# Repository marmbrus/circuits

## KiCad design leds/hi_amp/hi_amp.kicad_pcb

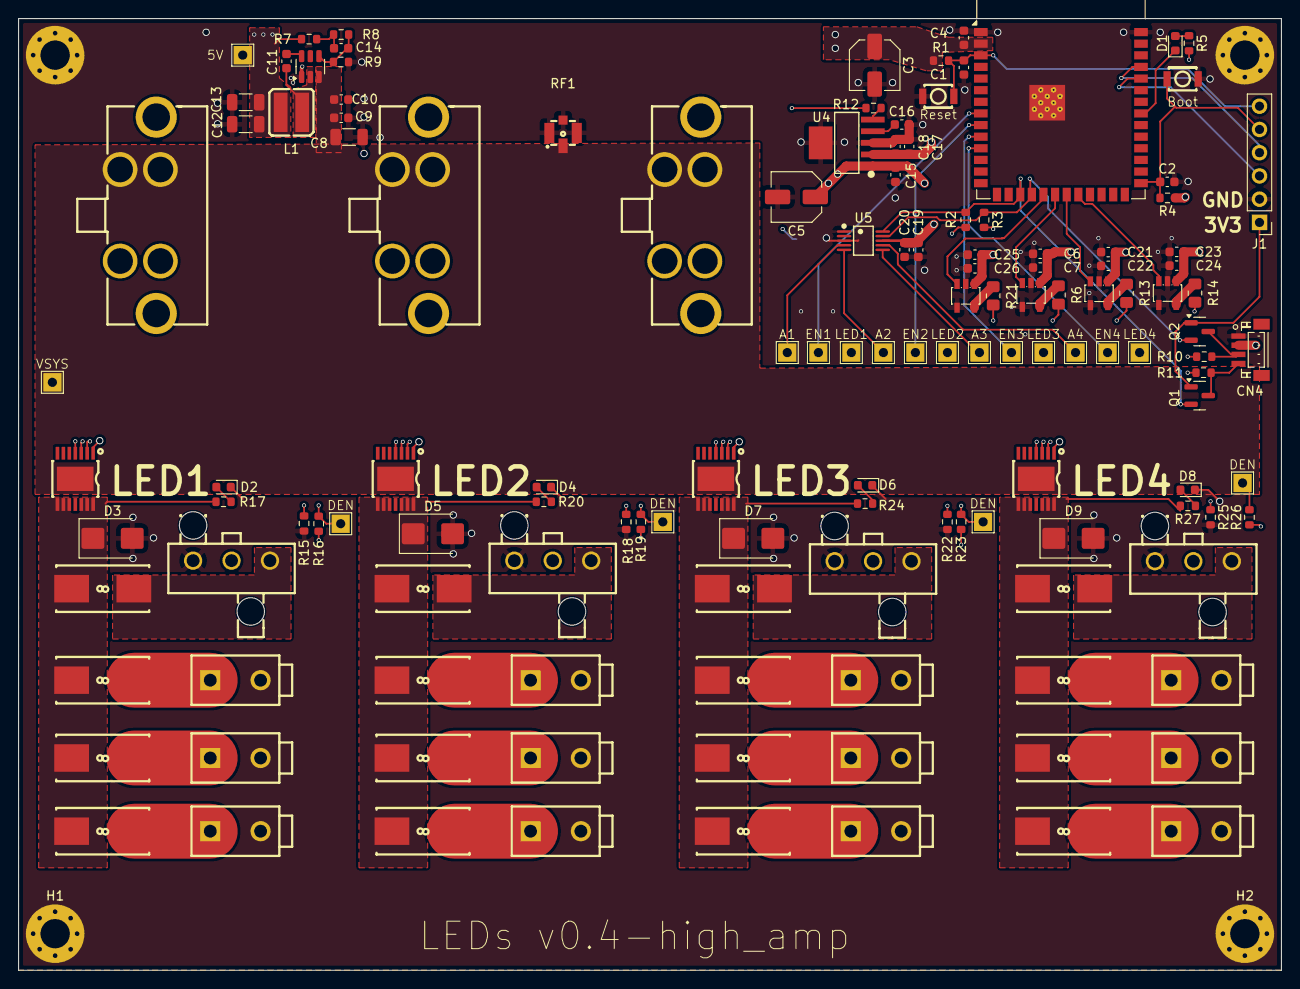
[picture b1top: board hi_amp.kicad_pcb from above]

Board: 4 copper layers, 138.0 x 104.0 mm, 140 parts (1 on the bottom side), 68 nets.

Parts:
C1: 10uf; C_0603_1608Metric
C2: 1uf; C_0603_1608Metric
C3, C5: 22uF; C_Elec_5x5.8
C4, C7, C10, C20, C22, C24, C26: 100nF; C_0603_1608Metric
C6, C9, C21, C23, C25: 10uF; C_0603_1608Metric
C8, C12, C13: 22uF; C_1206_3216Metric
C11: 100nf; C_0603_1608Metric
C14: 75pF; C_0603_1608Metric
C15, C17, C18, C19: 1uF; C_0603_1608Metric
C16: 10nF; C_0603_1608Metric
CN1, CN2, CN3: 428192213; CONN-TH_0428192214
CN4: BM04B-SRSS-TB(LF)(SN); CONN-SMD_BM04B-SRSS-TB
CN5, CN9, CN13, CN17: 39302030; CONN-TH_3P-P4.20_39302030
CN6, CN7, CN8, CN10, CN11, CN12, CN14, CN15, CN16, CN18, CN19, CN20: 39288020; CONN-TH_39288020
D1, D2, D4, D6, D8: LED; LED_0603_1608Metric
D3, D5, D7, D9: D_TVS; D_SMB
FH1, FH2, FH3, FH4, FH5, FH6, FH7, FH8, FH9, FH10, FH11, FH12, FH13, FH14, FH15, FH16: 01550900M; FUSE-SMD_L9.8-W5.0_01550900M
H1, H2, H3, H4: MountingHole_Pad; MountingHole_3.2mm_M3_Pad_Via
J1: Conn_01x06; PinHeader_1x06_P2.54mm_Vertical
L1: XGL4040-153MEC; IND-SMD_L4.0-W4.0_XAL4040-103
Q1, Q2: BSS138; SOT-23
R1, R2, R3, R4, R10, R11, R12: 10k; R_0603_1608Metric
R5: 330; R_0603_1608Metric
R6, R13, R14, R21: 120; R_0805_2012Metric_Pad1.20x1.40mm_HandSolder
R7: 49.9; R_0603_1608Metric
R8: 100k; R_0603_1608Metric
R9: 13.3k; R_0603_1608Metric
R15, R18, R22, R25: 1.5k; R_0603_1608Metric
R16, R19, R23, R26: 4.7k; R_0603_1608Metric
R17, R20, R24, R27: 3.3k; R_0603_1608Metric
RF1, RF2: 73412-0110; ANT-SMD_73412-0110
SW1, SW2: KEY-SMD_B3U-1000PM
TP1, TP2, TP3, TP4, TP5, TP6, TP7, TP8, TP9, TP10, TP11, TP12, TP13, TP14, TP15, TP16, TP17, TP18: LabeledTestPoint
U1: ESP32-S3-WROOM-1
U2, U6, U7, U10: UCC27517DBVR; SOT-23-5_L3.0-W1.7-P0.95-LS2.8-BR
U3: TPS54202DDC; SOT-23-6
U4: TPS73733DCQ_C5220270; SOT-223-6_L6.5-W3.5-P1.27-LS7.0-BR
U5: ADS1115IDGSR; MSOP-10_L3.0-W3.0-P0.50-LS5.0-BL
U8, U9, U11, U12: BTS70021EPPXUMA1; PG-TSDSO-14_L4.9-W3.9-P0.65-LS6.0-BL-EP

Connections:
/3v3/3v3: C3.1, C4.1, C17.1, C18.1, J1.1, Q1.1 (G), Q2.1 (G), R1.1, R2.1, R3.1, R4.1, R5.2, U1.2 (3V3), U4.2 (OUT)
/5V: C5.1, C6.1, C7.1, C12.1, C13.1, C15.1, C19.1, C20.1, C21.1, C22.1, C23.1, C24.1, C25.1, C26.1, CN4.2, L1.2, R7.1, R10.1, R11.1, R12.1, R16.1, R19.1, R23.1, R26.1, RF2.2 (SIG), TP14.1, U2.1 (VDD), U4.1 (IN), U5.8 (VDD), U6.1 (VDD), U7.1 (VDD), U10.1 (VDD)
/VSYS: C8.1, C9.1, C10.1, CN1.2, CN1.4, CN2.2, CN2.4, CN3.2, CN3.4, RF1.2 (SIG), TP1.1, U3.3 (VIN), U8.15 (VS), U9.15 (VS), U11.15 (VS), U12.15 (VS)
/a2d/AIN1: R15.1, TP6.1, U5.4 (AIN0), U8.4 (IS)
/a2d/AIN2: R18.1, TP8.1, U5.5 (AIN1), U9.4 (IS)
/a2d/AIN3: R22.1, TP10.1, U5.6 (AIN2), U11.4 (IS)
/a2d/AIN4: R25.1, TP12.1, U5.7 (AIN3), U12.4 (IS)
/a2d/I2C.SCL: Q1.2 (S), R2.2, U1.17 (IO9), U5.10 (SCL)
/a2d/I2C.SDA: Q2.2 (S), R3.2, U1.18 (IO10), U5.9 (SDA)
/buckconverter/FB: C14.1, R8.2, R9.1, U3.4 (FB)
/buckconverter/SW: C11.2, L1.1, U3.2 (SW)
/esp32/EN1: TP7.1, U1.8 (IO15), U8.2 (IN)
/esp32/EN2: TP9.1, U1.9 (IO16), U9.2 (IN)
/esp32/EN3: TP11.1, U1.10 (IO17), U11.2 (IN)
/esp32/EN4: TP13.1, U1.11 (IO18), U12.2 (IN)
/esp32/LED1: CN5.2, R21.1, TP2.1
/esp32/LED2: CN9.2, R6.1, TP3.1
/esp32/LED3: CN13.2, R13.1, TP4.1
/esp32/LED4: CN17.2, R14.1, TP5.1
/esp32/driver1/IN: U1.20 (IO12), U2.3 (IN+)
/esp32/driver2/IN: U1.21 (IO13), U6.3 (IN+)
/esp32/driver3/IN: U1.22 (IO14), U7.3 (IN+)
/esp32/driver/IN: U1.19 (IO11), U10.3 (IN+)
/led_channel1/Fused1: CN9.1, FH5.2
/led_channel1/Switched12V: D5.1 (K), FH5.1, FH6.1, FH7.1, FH8.1, R20.1, U9.8 (OUT), U9.9 (OUT), U9.10 (OUT), U9.12 (OUT), U9.13 (OUT), U9.14 (OUT)
/led_channel2/Fused1: CN13.1, FH9.2
/led_channel2/Switched12V: D7.1 (K), FH9.1, FH10.1, FH11.1, FH12.1, R24.1, U11.8 (OUT), U11.9 (OUT), U11.10 (OUT), U11.12 (OUT), U11.13 (OUT), U11.14 (OUT)
/led_channel3/Fused1: CN17.1, FH13.2
/led_channel3/Switched12V: D9.1 (K), FH13.1, FH14.1, FH15.1, FH16.1, R27.1, U12.8 (OUT), U12.9 (OUT), U12.10 (OUT), U12.12 (OUT), U12.13 (OUT), U12.14 (OUT)
/led_channel/Fused1: CN5.1, FH1.2
/led_channel/Switched12V: D3.1 (K), FH1.1, FH2.1, FH3.1, FH4.1, R17.1, U8.8 (OUT), U8.9 (OUT), U8.10 (OUT), U8.12 (OUT), U8.13 (OUT), U8.14 (OUT)
GND: C1.2, C2.2, C3.2, C4.2, C5.2, C6.2, C7.2, C8.2, C9.2, C10.2, C12.2, C13.2, C15.2, C16.2, C17.2, C18.2, C19.2, C20.2, C21.2, C22.2, C23.2, C24.2, C25.2, C26.2, CN1.1, CN1.3, CN2.1, CN2.3, CN3.1, CN3.3, CN4.1, CN5.3, CN6.2, CN7.2, CN8.2, CN9.3, CN10.2, CN11.2, CN12.2, CN13.3, CN14.2, CN15.2, CN16.2, CN17.3, CN18.2, CN19.2, CN20.2, D2.1 (K), D3.2 (A), D4.1 (K), D5.2 (A), D6.1 (K), D7.2 (A), D8.1 (K), D9.2 (A), H1.1, H2.1, H3.1, H4.1, J1.2, R9.2, R15.2, R18.2, R22.2, R25.2, RF1.1 (GND), RF1.3 (GND), RF1.4 (GND), RF2.1 (GND), RF2.3 (GND), RF2.4 (GND), SW1.1, SW2.1, U1.1 (GND), U1.40 (GND), U1.41 (GND), U2.2 (GND), U2.4 (IN-), U3.1 (GND), U4.3 (GND), U4.6 (GND), U5.1 (ADDR), U5.3 (GND), U6.2 (GND), U6.4 (IN-), U7.2 (GND), U7.4 (IN-), U8.1 (GND), U9.1 (GND), U10.2 (GND), U10.4 (IN-), U11.1 (GND), U12.1 (GND)
unnamed: C14.2, R7.2, R8.1
unnamed: CN6.1, FH2.2
unnamed: CN7.1, FH3.2
unnamed: CN8.1, FH4.2
unnamed: CN10.1, FH6.2
unnamed: CN11.1, FH7.2
unnamed: CN12.1, FH8.2
unnamed: CN14.1, FH10.2
unnamed: CN15.1, FH11.2
unnamed: CN16.1, FH12.2
unnamed: CN18.1, FH14.2
unnamed: CN19.1, FH15.2
unnamed: CN20.1, FH16.2
unnamed: D1.2 (A), R5.1
unnamed: D1.1 (K), U1.33 (IO40)
unnamed: D2.2 (A), R17.2
unnamed: D4.2 (A), R20.2
unnamed: D6.2 (A), R24.2
unnamed: D8.2 (A), R27.2
unnamed: J1.3, U1.36 (RXD0)
unnamed: J1.4, U1.37 (TXD0)
unnamed: C2.1, J1.5, R4.2, SW2.2, U1.27 (IO0)
unnamed: C1.1, J1.6, R1.2, SW1.2, U1.3 (EN)
unnamed: CN4.4, Q1.3 (D), R11.2
unnamed: CN4.3, Q2.3 (D), R10.2
unnamed: R6.2, U2.5 (OUT)
unnamed: C11.1, U3.6 (BOOT)
unnamed: R12.2, U4.5 (EN)
unnamed: C16.1, U4.4 (NR/FB)
unnamed: R13.2, U6.5 (OUT)
unnamed: R14.2, U7.5 (OUT)
unnamed: R16.2, TP15.1, U8.3 (DEN)
unnamed: R19.2, TP16.1, U9.3 (DEN)
unnamed: R21.2, U10.5 (OUT)
unnamed: R23.2, TP17.1, U11.3 (DEN)
unnamed: R26.2, TP18.1, U12.3 (DEN)

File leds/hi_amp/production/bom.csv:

Designator,Footprint,Quantity,Value,LCSC Part #
"C1, C21, C23, C25, C6, C9",0603,6,10uf,
"C10, C11, C20, C22, C24, C26, C4, C7",0603,8,100nF,
"C12, C13, C8",1206,3,22uF,
C14,0603,1,75pF,
"C15, C17, C18, C19, C2",0603,5,1uF,
C16,0603,1,10nF,
"C3, C5",C_Elec_5x5.8,2,22uF,C336246
"CN1, CN2",CONN-TH_0428192214,2,428192213,C563817
"CN10, CN11, CN12, CN14, CN15, CN16, CN18, CN19, CN20, CN6, CN7, CN8",CONN-TH_39288020,12,39288020,C490534
"CN13, CN17, CN5, CN9",CONN-TH_3P-P4.20_39302030,4,39302030,C589033
CN4,CONN-SMD_BM04B-SRSS-TB,1,BM04B-SRSS-TB(LF)(SN),C160390
D1,0603,1,LED,C2290
"D2, D4, D6, D8",0603,4,LED,C2286
"D3, D5, D7, D9",D_SMB,4,D_TVS,C151256
"FH1, FH10, FH11, FH12, FH13, FH14, FH15, FH16, FH2, FH3, FH4, FH5, FH6, FH7, FH8, FH9",FUSE-SMD_L9.8-W5.0_01550900M,16,01550900M,C108518
L1,IND-SMD_L4.0-W4.0_XAL4040-103,1,XGL4040-153MEC,C3911667
"Q1, Q2",SOT-23,2,BSS138,
"R1, R10, R11, R12, R2, R3, R4",0603,7,10k,
"R13, R14, R21, R6",0805,4,120,
"R15, R18, R22, R25",0603,4,1.5k,
"R16, R19, R23, R26",0603,4,4.7k,
"R17, R20, R24, R27",0603,4,3.3k,
R5,0603,1,330,
R7,0603,1,49.9,
R8,0603,1,100k,
R9,0603,1,13.3k,
"SW1, SW2",KEY-SMD_B3U-1000PM,2,KEY-SMD_B3U-1000PM,C231329
U1,ESP32-S3-WROOM-1,1,ESP32-S3-WROOM-1,
"U10, U2, U6, U7",SOT-23-5_L3.0-W1.7-P0.95-LS2.8-BR,4,UCC27517DBVR,C99395
"U11, U12, U8, U9",PG-TSDSO-14_L4.9-W3.9-P0.65-LS6.0-BL-EP,4,BTS70021EPPXUMA1,C2680407
U3,SOT-23-6,1,TPS54202DDC,
U4,SOT-223-6_L6.5-W3.5-P1.27-LS7.0-BR,1,TPS73733DCQ_C5220270,C5220270
U5,MSOP-10_L3.0-W3.0-P0.50-LS5.0-BL,1,ADS1115IDGSR,C37593

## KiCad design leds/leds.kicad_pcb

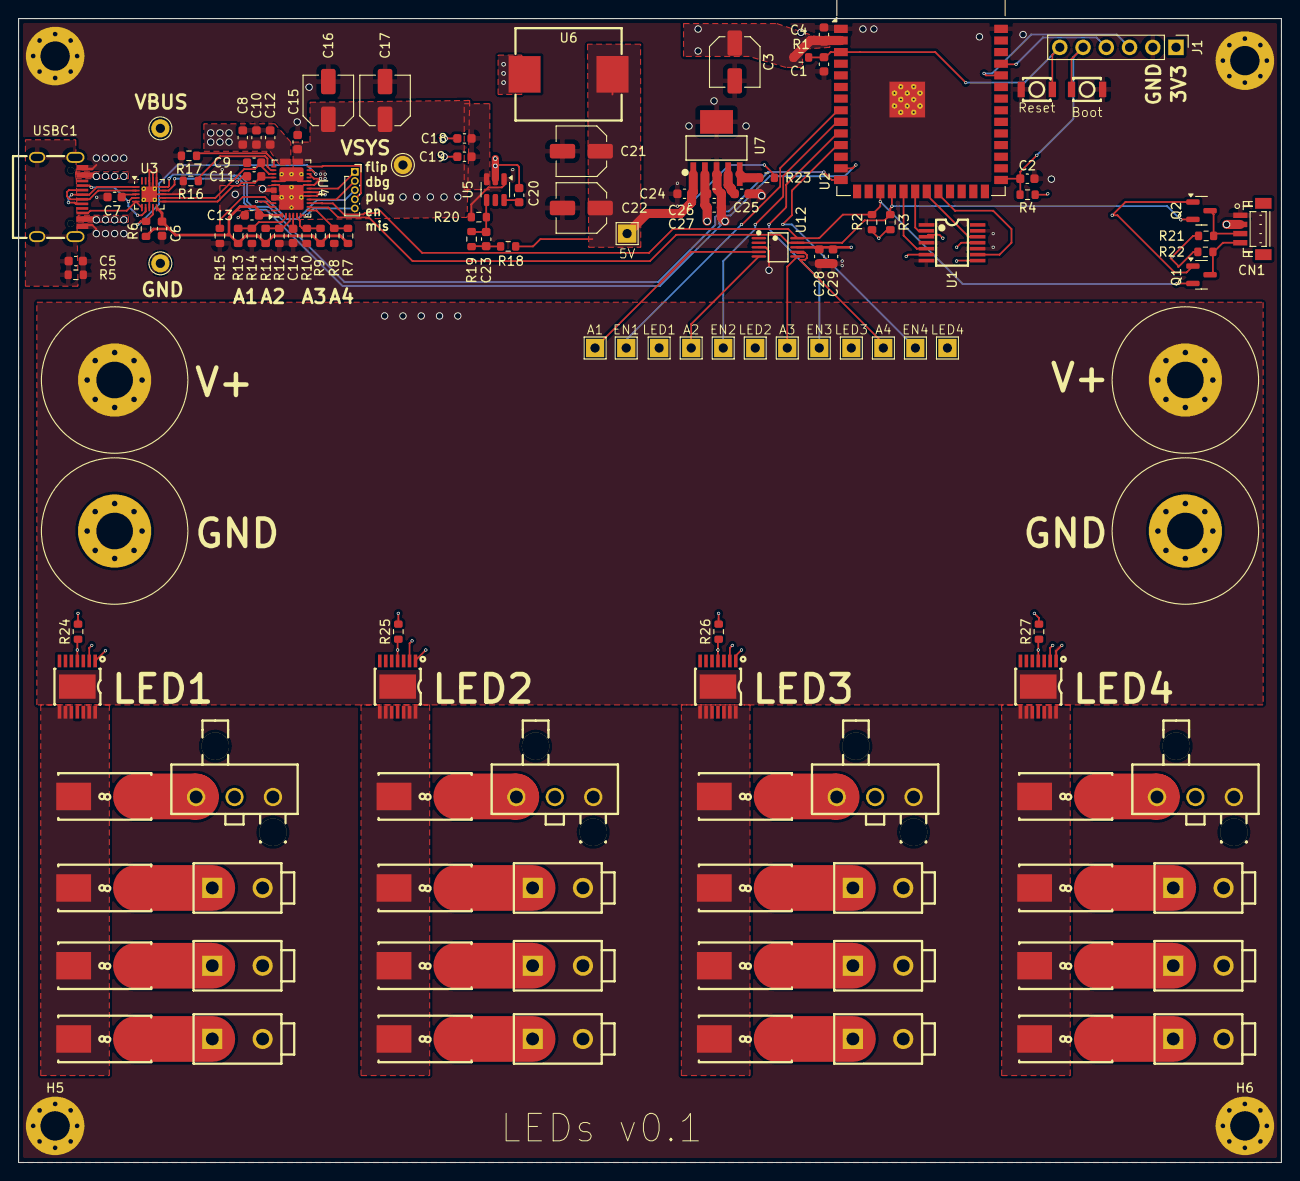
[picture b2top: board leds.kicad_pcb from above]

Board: 4 copper layers, 138.0 x 125.0 mm, 132 parts (0 on the bottom side), 81 nets.

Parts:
C1: 10uf; C_0603_1608Metric
C2: 1uf; C_0603_1608Metric
C3, C16, C17, C21, C22: 22uF; C_Elec_5x5.8
C4, C5, C7, C10, C19, C28: 100nF; C_0603_1608Metric
C6, C24, C26, C27, C29: 1uF; C_0603_1608Metric
C8, C14: 4.7uF; C_0603_1608Metric
C9, C11: 330pF; C_0603_1608Metric
C12, C25: 10nF; C_0603_1608Metric
C13, C15, C18: 10uF; C_0603_1608Metric
C20: 100nf; C_0603_1608Metric
C23: 75pF; C_0603_1608Metric
CN1: BM04B-SRSS-TB(LF)(SN); CONN-SMD_BM04B-SRSS-TB
CN2, CN6, CN10, CN14: 39302030; CONN-TH_3P-P4.20_39302030
CN3, CN4, CN5, CN7, CN8, CN9, CN11, CN12, CN13, CN15, CN16, CN17: 39288020; CONN-TH_39288020
FH1, FH2, FH3, FH4, FH5, FH6, FH7, FH8, FH9, FH10, FH11, FH12, FH13, FH14, FH15, FH16: 01550900M; FUSE-SMD_L9.8-W5.0_01550900M
H1, H2, H3, H4: MountingHole_Pad; MountingHole_4mm_Pad_Via
H5, H6, H7, H8: MountingHole_Pad; MountingHole_3.2mm_M3_Pad_Via
J1: Conn_01x06; PinHeader_1x06_P2.54mm_Vertical
J2: Conn_01x05_Pin; PinSocket_1x05_P1.00mm_Vertical
Q1, Q2: BSS138; SOT-23
R1, R2, R3, R4, R6, R15, R16, R17, R21, R22, R23: 10k; R_0603_1608Metric
R5: 1M; R_0603_1608Metric
R7, R11: 162k; R_0603_1608Metric
R8, R12: 38.3k; R_0603_1608Metric
R9: 191k; R_0603_1608Metric
R10: 9.31k; R_0603_1608Metric
R13: 196k; R_0603_1608Metric
R14: 2.2k; R_0603_1608Metric
R18: 49.9; R_0603_1608Metric
R19: 100k; R_0603_1608Metric
R20: 13.3k; R_0603_1608Metric
R24, R25, R26, R27: 820; R_0603_1608Metric
SW1, SW2: KEY-SMD_B3U-1000PM
TP1: VBUS; Pin_D1.0mm_L10.0mm
TP2: GND; Pin_D1.0mm_L10.0mm
TP3: VSYS; Pin_D1.0mm_L10.0mm
TP4, TP5, TP6, TP7, TP8, TP9, TP10, TP11, TP12, TP13, TP14, TP15, TP16: LabeledTestPoint
U1: SN74AHCT125PWR; TSSOP-14_L5.0-W4.4-P0.65-LS6.4-BL
U2: ESP32-S3-WROOM-1
U3: TPD6S300A; WQFN-20-1EP_3x3mm_P0.4mm_EP1.7x1.7mm_ThermalVias
U4: TPS25730D; Texas_REF0038A_WQFN-38-2EP_6x4mm_P0.4
U5: TPS54202DDC; SOT-23-6
U6: CYA1040-15UH; IND-SMD_L11.6-W10.1
U7: TPS73733DCQ_C5220270; SOT-223-6_L6.5-W3.5-P1.27-LS7.0-BR
U8, U9, U10, U11: BTS70021EPPXUMA1; PG-TSDSO-14_L4.9-W3.9-P0.65-LS6.0-BL-EP
U12: ADS1115IDGSR; MSOP-10_L3.0-W3.0-P0.50-LS5.0-BL
USBC1: TYPE-C-31-M-12; USB-C_SMD-TYPE-C-31-M-12

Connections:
/3v3/3v3: C3.1, C4.1, C26.1, C27.1, J1.1, Q1.1 (G), Q2.1 (G), R1.1, R2.1, R3.1, R4.1, U2.2 (3V3), U7.2 (OUT)
/5V: C21.1, C22.1, C24.1, C28.1, C29.1, CN1.2, R18.1, R21.1, R22.1, R23.1, TP4.1, U6.2, U7.1 (IN), U12.8 (VDD)
/a2d/AIN1: R24.1, TP13.1, U8.4 (IS), U12.4 (AIN0)
/a2d/AIN2: R25.1, TP14.1, U9.4 (IS), U12.5 (AIN1)
/a2d/AIN3: R26.1, TP15.1, U10.4 (IS), U12.6 (AIN2)
/a2d/AIN4: R27.1, TP16.1, U11.4 (IS), U12.7 (AIN3)
/a2d/I2C.SCL: Q1.2 (S), R2.2, U2.17 (IO9), U4.9 (I2Ct_SCL), U12.10 (SCL)
/a2d/I2C.SDA: Q2.2 (S), R3.2, U2.18 (IO10), U4.8 (I2Ct_SDA), U12.9 (SDA)
/buckconverter/FB: C23.1, R19.2, R20.1, U5.4 (FB)
/buckconverter/SW: C20.2, U5.2 (SW), U6.1
/buckconverter/VIN: C15.1, C16.1, C17.1, C18.1, C19.1, H1.1, H2.1, TP3.1, U4.20 (PPHV), U5.3 (VIN), U8.15 (VS), U9.15 (VS), U10.15 (VS), U11.15 (VS)
/esp32/EN1: TP9.1, U2.8 (IO15), U8.2 (IN)
/esp32/EN2: TP10.1, U2.9 (IO16), U9.2 (IN)
/esp32/EN3: TP11.1, U2.10 (IO17), U10.2 (IN)
/esp32/EN4: TP12.1, U2.11 (IO18), U11.2 (IN)
/esp32/LED1: CN2.2, TP5.1, U1.6 (2Y)
/esp32/LED2: CN6.2, TP6.1, U1.3 (1Y)
/esp32/LED3: CN10.2, TP7.1, U1.11 (4Y)
/esp32/LED4: CN14.2, TP8.1, U1.8 (3Y)
/esp32/USB.DN: U2.13 (IO19), U3.14 (SBU2)
/esp32/USB.DP: U2.14 (IO20), U3.15 (SBU1)
/led_channel1/Switched12V: FH5.1, FH6.1, FH7.1, FH8.1, U9.8 (OUT), U9.9 (OUT), U9.10 (OUT), U9.12 (OUT), U9.13 (OUT), U9.14 (OUT)
/led_channel2/Switched12V: FH9.1, FH10.1, FH11.1, FH12.1, U10.8 (OUT), U10.9 (OUT), U10.10 (OUT), U10.12 (OUT), U10.13 (OUT), U10.14 (OUT)
/led_channel3/Switched12V: FH13.1, FH14.1, FH15.1, FH16.1, U11.8 (OUT), U11.9 (OUT), U11.10 (OUT), U11.12 (OUT), U11.13 (OUT), U11.14 (OUT)
/led_channel/Switched12V: FH1.1, FH2.1, FH3.1, FH4.1, U8.8 (OUT), U8.9 (OUT), U8.10 (OUT), U8.12 (OUT), U8.13 (OUT), U8.14 (OUT)
/usbcpd/VBUS: C8.1, C10.1, C12.1, TP1.1, U4.23 (VBUS_IN), U4.32 (VBUS), USBC1.A4 (VBUS), USBC1.A9 (VBUS), USBC1.B4 (VBUS), USBC1.B9 (VBUS)
/usbcpd/fault: R6.2, U3.9 (~FLT), U4.18 (~FAULT_IN)
/usbcpd/shield: C5.1, R5.1, USBC1.0 (SH), USBC1.1 (SH), USBC1.2 (SH), USBC1.3 (SH)
GND: C1.2, C2.2, C3.2, C4.2, C5.2, C6.2, C7.2, C8.2, C9.2, C10.2, C11.2, C12.2, C13.2, C14.2, C15.2, C16.2, C17.2, C18.2, C19.2, C21.2, C22.2, C24.2, C25.2, C26.2, C27.2, C28.2, C29.2, CN1.1, CN2.3, CN3.2, CN4.2, CN5.2, CN6.3, CN7.2, CN8.2, CN9.2, CN10.3, CN11.2, CN12.2, CN13.2, CN14.3, CN15.2, CN16.2, CN17.2, H3.1, H4.1, H5.1, H6.1, H7.1, H8.1, J1.2, R5.2, R8.2, R10.2, R12.2, R14.2, R15.2, R16.2, R17.2, R20.2, R24.2, R25.2, R26.2, R27.2, SW1.1, SW2.1, TP2.1, U1.1 (~1OE), U1.4 (~2OE), U1.7 (GND), U1.10 (~3OE), U1.13 (~4OE), U2.1 (GND), U2.40 (GND), U2.41 (GND), U3.8 (GND), U3.13 (GND), U3.16 (GND), U3.17 (GND), U3.18 (GND), U3.21 (GND), U4.11 (GND), U4.12 (GND), U4.14 (GND), U4.16 (GND), U4.17 (GND), U4.31 (GND), U4.34 (GND), U4.39 (GND), U5.1 (GND), U7.3 (GND), U7.6 (GND), U8.1 (GND), U9.1 (GND), U10.1 (GND), U11.1 (GND), U12.3 (GND), USBC1.A1 (GND), USBC1.A12 (GND), USBC1.B1 (GND), USBC1.B12 (GND)
unnamed: C23.2, R18.2, R19.1
unnamed: CN2.1, FH1.2
unnamed: CN3.1, FH2.2
unnamed: CN4.1, FH3.2
unnamed: CN5.1, FH4.2
unnamed: CN6.1, FH5.2
unnamed: CN7.1, FH6.2
unnamed: CN8.1, FH7.2
unnamed: CN9.1, FH8.2
unnamed: CN10.1, FH9.2
unnamed: CN11.1, FH10.2
unnamed: CN12.1, FH11.2
unnamed: CN13.1, FH12.2
unnamed: CN14.1, FH13.2
unnamed: CN15.1, FH14.2
unnamed: CN16.1, FH15.2
unnamed: CN17.1, FH16.2
unnamed: J1.3, U2.36 (RXD0)
unnamed: J1.4, U2.37 (TXD0)
unnamed: C2.1, J1.5, R4.2, SW2.2, U2.27 (IO0)
unnamed: C1.1, J1.6, R1.2, SW1.2, U2.3 (EN)
unnamed: J2.1, U4.13 (PLUG_FLIP)
unnamed: J2.2, U4.10 (DBG_ACC)
unnamed: J2.3, U4.37 (PLUG_EVENT)
unnamed: J2.4, U4.19 (~SINK_EN)
unnamed: J2.5, U4.6 (CAP_MIS)
unnamed: CN1.4, Q1.3 (D), R22.2
unnamed: CN1.3, Q2.3 (D), R21.2
unnamed: R15.1, U4.36 (RESERVED)
unnamed: R16.1, U4.27 (RESERVED)
unnamed: R17.1, U4.26 (RESERVED)
unnamed: U1.2 (1A), U2.20 (IO12)
unnamed: U1.5 (2A), U2.19 (IO11)
unnamed: U1.9 (3A), U2.22 (IO14)
unnamed: U1.12 (4A), U2.21 (IO13)
unnamed: C9.1, U3.12 (CC1), U4.28 (CC1)
unnamed: C11.1, U3.11 (CC2), U4.29 (CC2)
unnamed: U3.4 (C_CC1), U3.7 (RPD_G1), USBC1.A5 (CC1)
unnamed: U3.5 (C_CC2), U3.6 (RPD_G2), USBC1.B5 (CC2)
unnamed: U3.1 (C_SBU1), USBC1.A6 (DP1), USBC1.B6 (DP2)
unnamed: U3.2 (C_SBU2), USBC1.A7 (DN1), USBC1.B7 (DN2)
unnamed: C7.1, U3.3 (VBIAS)
unnamed: C6.1, C13.1, R6.1, R7.1, R9.1, R11.1, R13.1, U3.10 (VPWR), U4.1 (LDO_3V3)
unnamed: R13.2, R14.1, U4.2 (ADCIN1)
unnamed: R11.2, R12.1, U4.3 (ADCIN2)
unnamed: R9.2, R10.1, U4.5 (ADCIN3)
unnamed: R7.2, R8.1, U4.7 (ADCIN4)
unnamed: U4.15 (DRAIN), U4.30 (DRAIN), U4.40 (DRAIN)
unnamed: C14.1, U4.4 (LDO_1V5)
unnamed: C20.1, U5.6 (BOOT)
unnamed: R23.2, U7.5 (EN)
unnamed: C25.1, U7.4 (NR/FB)

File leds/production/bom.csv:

Designator,Footprint,Quantity,Value,LCSC Part #
"C1, C13, C15, C18",0603,4,10uf,
"C10, C19, C20, C28, C4, C5, C7",0603,7,100nF,
"C11, C9",0603,2,330pF,
"C12, C25",0603,2,10nF,
"C14, C8",0603,2,4.7uF,
"C16, C17, C21, C22, C3",C_Elec_5x5.8,5,22uF,C336246
"C2, C24, C26, C27, C29, C6",0603,6,1uf,
C23,0603,1,75pF,
CN1,CONN-SMD_BM04B-SRSS-TB,1,BM04B-SRSS-TB(LF)(SN),C160390
"CN10, CN14, CN2, CN6",CONN-TH_3P-P4.20_39302030,4,39302030,C589033
"CN11, CN12, CN13, CN15, CN16, CN17, CN3, CN4, CN5, CN7, CN8, CN9",CONN-TH_39288020,12,39288020,C490534
"FH1, FH10, FH11, FH12, FH13, FH14, FH15, FH16, FH2, FH3, FH4, FH5, FH6, FH7, FH8, FH9",FUSE-SMD_L9.8-W5.0_01550900M,16,01550900M,C108518
"Q1, Q2",SOT-23,2,BSS138,
"R1, R15, R16, R17, R2, R21, R22, R23, R3, R4, R6",0603,11,10k,
R10,0603,1,9.31k,
"R11, R7",0603,2,162k,
"R12, R8",0603,2,38.3k,
R13,0603,1,196k,
R14,0603,1,2.2k,
R18,0603,1,49.9,
R19,0603,1,100k,
R20,0603,1,13.3k,
"R24, R25, R26, R27",0603,4,820,
R5,0603,1,1M,
R9,0603,1,191k,
"SW1, SW2",KEY-SMD_B3U-1000PM,2,KEY-SMD_B3U-1000PM,C231329
U1,TSSOP-14_L5.0-W4.4-P0.65-LS6.4-BL,1,SN74AHCT125PWR,C36365
"U10, U11, U8, U9",PG-TSDSO-14_L4.9-W3.9-P0.65-LS6.0-BL-EP,4,BTS70021EPPXUMA1,C2680407
U12,MSOP-10_L3.0-W3.0-P0.50-LS5.0-BL,1,ADS1115IDGSR,C37593
U2,ESP32-S3-WROOM-1,1,ESP32-S3-WROOM-1,
U3,WQFN-20-1EP_3x3mm_P0.4mm_EP1.7x1.7mm_ThermalVias,1,TPD6S300A,
U4,Texas_REF0038A_WQFN-38-2EP_6x4mm_P0.4,1,TPS25730D,
U5,SOT-23-6,1,TPS54202DDC,
U6,IND-SMD_L11.6-W10.1,1,CYA1040-15UH,C6364678
U7,SOT-223-6_L6.5-W3.5-P1.27-LS7.0-BR,1,TPS73733DCQ_C5220270,C5220270
USBC1,USB-C_SMD-TYPE-C-31-M-12,1,TYPE-C-31-M-12,C165948

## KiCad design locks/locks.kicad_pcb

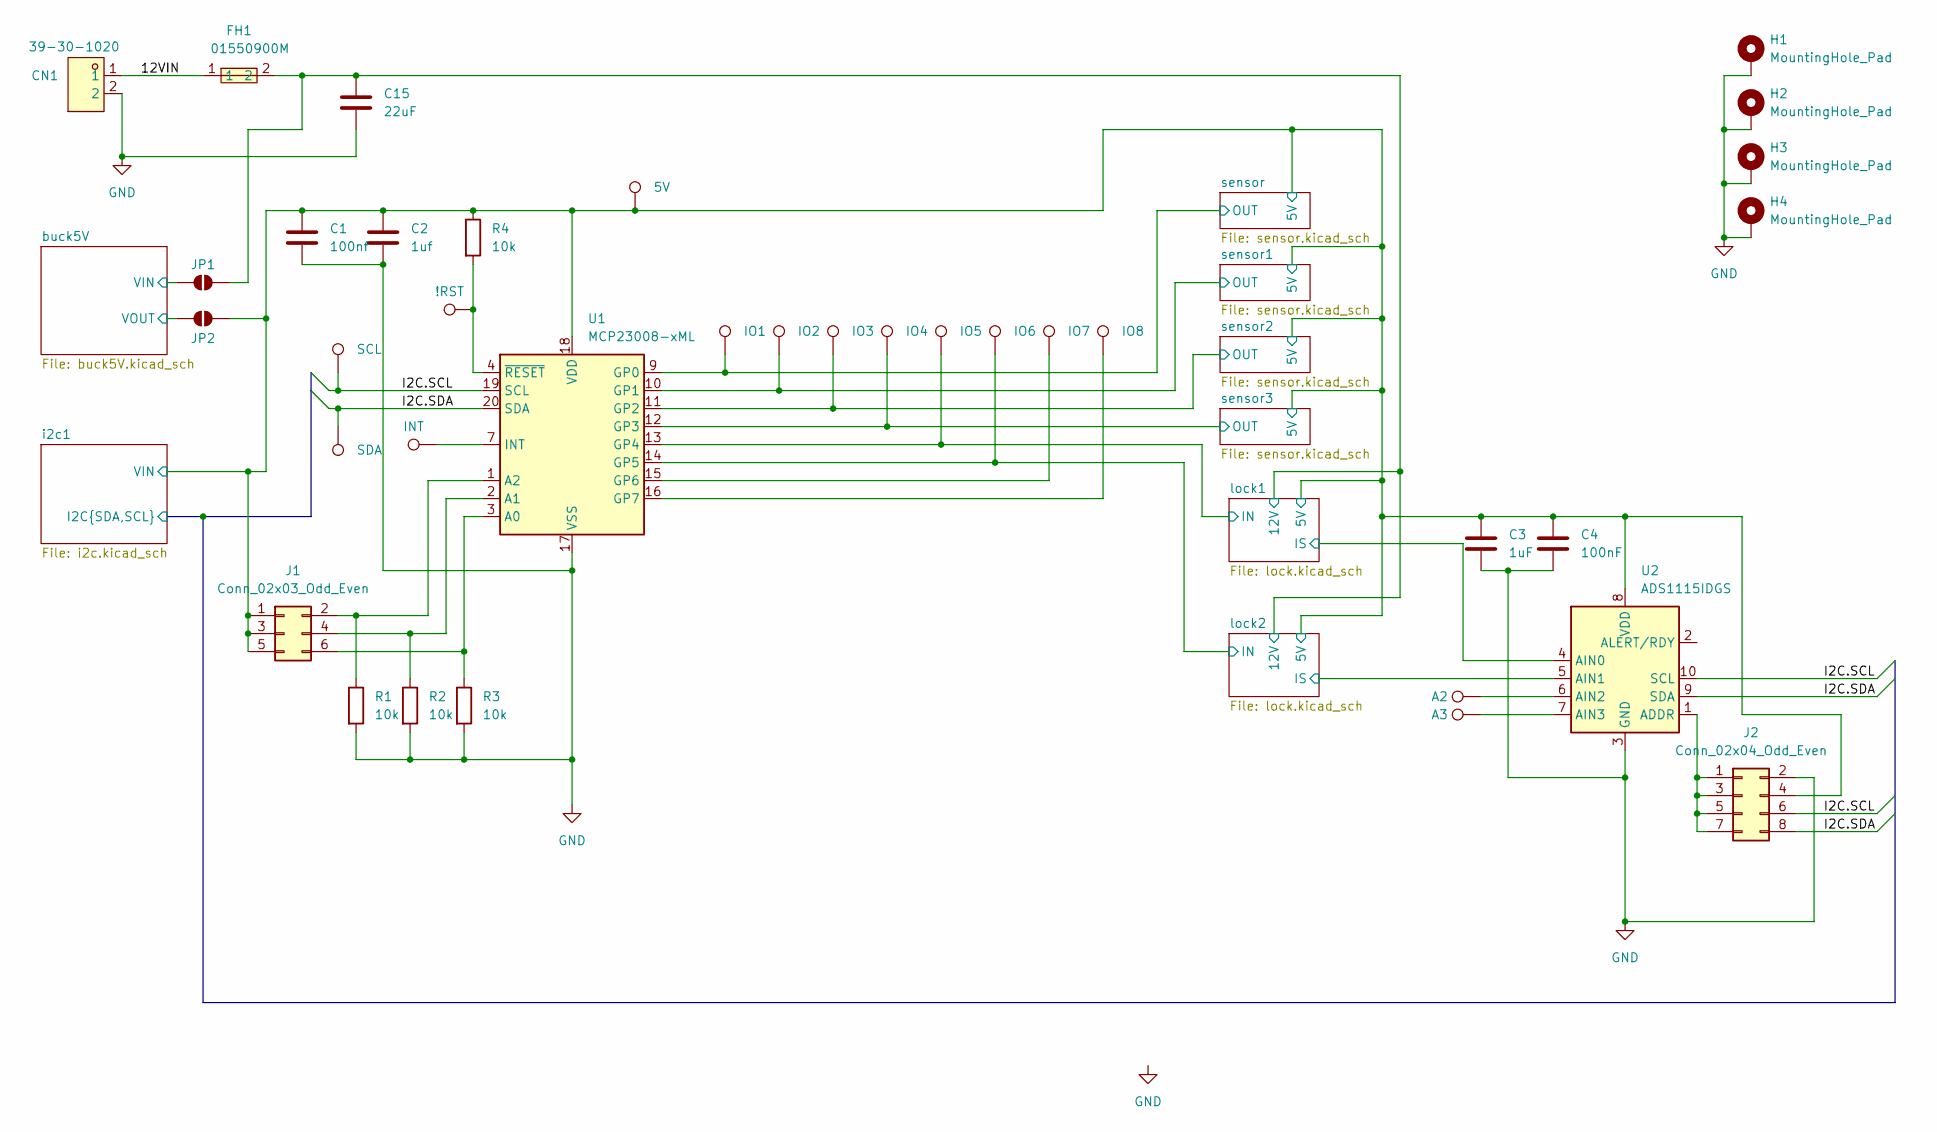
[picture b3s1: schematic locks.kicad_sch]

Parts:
C1: 100nf; C_0603_1608Metric
C2: 1uf; C_0603_1608Metric
C3: 1uF; C_0603_1608Metric
C4: 100nF; C_0603_1608Metric
C15: 22uF; C_1206_3216Metric
CN1: 39-30-1020; CONN-TH_2P-P5.50_39-30-1020; LCSC Part C240832
FH1: 01550900M; FUSE-SMD_L9.8-W5.0_01550900M; LCSC Part C108518
H1, H2, H3, H4: MountingHole_Pad; MountingHole_4.3mm_M4_ISO7380_Pad
J1: Conn_02x03_Odd_Even; PinHeader_2x03_P2.54mm_Vertical; LCSC Part C7501274
J2: Conn_02x04_Odd_Even; PinHeader_2x04_P2.54mm_Vertical
JP1, JP2: SolderJumper_2_Open; SolderJumper-2_P1.3mm_Open_Pad1.0x1.5mm
R1, R2, R3, R4: 10k; R_0603_1608Metric
TP1, TP2, TP3, TP4, TP5, TP6, TP7, TP8, TP9, TP10, TP11, TP12, TP13, TP14, TP16: LabeledTestPoint
U1: MCP23008-xML; QFN-20-1EP_4x4mm_P0.5mm_EP2.7x2.7mm; LCSC Part C144211
U2: ADS1115IDGS; TSSOP-10_3x3mm_P0.5mm

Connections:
/12VIN: CN1.1, FH1.1
/buck5V/VIN: JP1.1 (A); also elsewhere on the board
/buck5V/VOUT: JP2.1 (A); also elsewhere on the board
/i2c1/I2C.SCL: J2.6, TP1.1, U1.19 (SCL), U2.10 (SCL); also elsewhere on the board
/i2c1/I2C.SDA: J2.8, TP2.1, U1.20 (SDA), U2.9 (SDA); also elsewhere on the board
/i2c1/VIN: C1.1, C2.1, C3.1, C4.1, J1.1, J1.3, J1.5, J2.4, JP2.2 (B), R4.1, TP16.1, U1.18 (VDD), U2.8 (VDD); also elsewhere on the board
/lock1/12V: C15.1, FH1.2, JP1.2 (B); also elsewhere on the board
/lock1/IN: TP9.1, U1.13 (GP4); also elsewhere on the board
/lock1/IS: U2.4 (AIN0); also elsewhere on the board
/lock2/IN: TP10.1, U1.14 (GP5); also elsewhere on the board
/lock2/IS: U2.5 (AIN1); also elsewhere on the board
/sensor1/OUT: TP6.1, U1.10 (GP1); also elsewhere on the board
/sensor2/OUT: TP7.1, U1.11 (GP2); also elsewhere on the board
/sensor3/OUT: TP8.1, U1.12 (GP3); also elsewhere on the board
/sensor/OUT: TP5.1, U1.9 (GP0); also elsewhere on the board
GND: C1.2, C2.2, C3.2, C4.2, C15.2, CN1.2, H1.1, H2.1, H3.1, H4.1, J2.2, R1.2, R2.2, R3.2, U1.17 (VSS), U2.3 (GND); also elsewhere on the board
unnamed: J1.2, R1.1, U1.1 (A2)
unnamed: J1.4, R2.1, U1.2 (A1)
unnamed: J1.6, R3.1, U1.3 (A0)
unnamed: J2.1, J2.3, J2.5, J2.7, U2.1 (ADDR)
unnamed: TP11.1, U1.15 (GP6)
unnamed: TP12.1, U1.16 (GP7)
unnamed: TP3.1, U1.7 (INT)
unnamed: R4.2, TP4.1, U1.4 (~RESET)
unnamed: TP13.1, U2.6 (AIN2)
unnamed: TP14.1, U2.7 (AIN3)

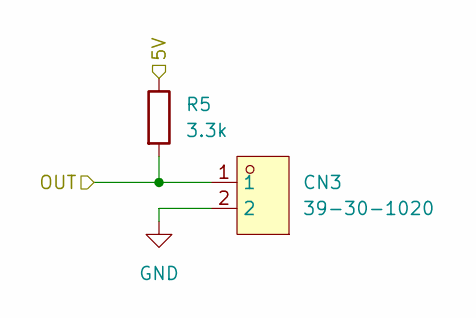
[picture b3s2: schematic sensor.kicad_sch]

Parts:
CN3: 39-30-1020; CONN-TH_2P-P5.50_39-30-1020; LCSC Part C240832
R5: 3.3k; R_0805_2012Metric

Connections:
/i2c1/VIN: R5.1; also elsewhere on the board
/sensor/OUT: CN3.1, R5.2; also elsewhere on the board
GND: CN3.2; also elsewhere on the board

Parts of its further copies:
CN4, CN5, CN6: 39-30-1020; CONN-TH_2P-P5.50_39-30-1020; LCSC Part C240832
R6, R7, R8: 3.3k; R_0805_2012Metric

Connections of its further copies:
/i2c1/VIN: R6.1, R7.1, R8.1; also elsewhere on the board
/sensor1/OUT: CN4.1, R6.2; also elsewhere on the board
/sensor2/OUT: CN5.1, R7.2; also elsewhere on the board
/sensor3/OUT: CN6.1, R8.2; also elsewhere on the board
GND: CN4.2, CN5.2, CN6.2; also elsewhere on the board

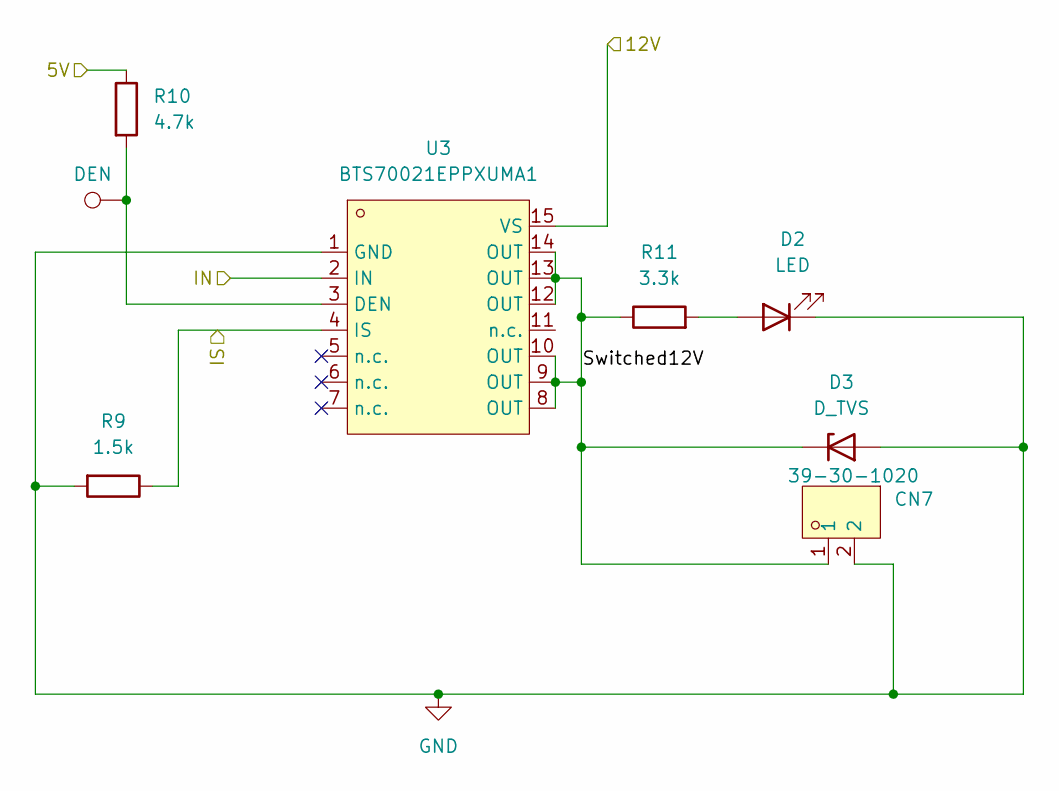
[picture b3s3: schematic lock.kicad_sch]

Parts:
CN7: 39-30-1020; CONN-TH_2P-P5.50_39-30-1020; LCSC Part C240832
D2: LED; LED_0603_1608Metric; LCSC Part C2286
D3: D_TVS; D_SMB; LCSC Part C151256
R9: 1.5k; R_0603_1608Metric
R10: 4.7k; R_0603_1608Metric
R11: 3.3k; R_0603_1608Metric
TP15: LabeledTestPoint
U3: BTS70021EPPXUMA1; PG-TSDSO-14_L4.9-W3.9-P0.65-LS6.0-BL-EP; LCSC Part C2680407

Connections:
/i2c1/VIN: R10.1; also elsewhere on the board
/lock1/12V: U3.15 (VS); also elsewhere on the board
/lock1/IN: U3.2 (IN); also elsewhere on the board
/lock1/IS: R9.1, U3.4 (IS); also elsewhere on the board
/lock1/Switched12V: CN7.1, D3.1 (K), R11.1, U3.8 (OUT), U3.9 (OUT), U3.10 (OUT), U3.12 (OUT), U3.13 (OUT), U3.14 (OUT)
GND: CN7.2, D2.1 (K), D3.2 (A), R9.2, U3.1 (GND); also elsewhere on the board
unnamed: D2.2 (A), R11.2
unnamed: R10.2, TP15.1, U3.3 (DEN)

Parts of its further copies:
CN8: 39-30-1020; CONN-TH_2P-P5.50_39-30-1020; LCSC Part C240832
D4: LED; LED_0603_1608Metric; LCSC Part C2286
D5: D_TVS; D_SMB; LCSC Part C151256
R15: 1.5k; R_0603_1608Metric
R16: 4.7k; R_0603_1608Metric
R17: 3.3k; R_0603_1608Metric
TP17: LabeledTestPoint
U6: BTS70021EPPXUMA1; PG-TSDSO-14_L4.9-W3.9-P0.65-LS6.0-BL-EP; LCSC Part C2680407

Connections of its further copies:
/i2c1/VIN: R16.1; also elsewhere on the board
/lock1/12V: U6.15 (VS); also elsewhere on the board
/lock2/IN: U6.2 (IN); also elsewhere on the board
/lock2/IS: R15.1, U6.4 (IS); also elsewhere on the board
/lock2/Switched12V: CN8.1, D5.1 (K), R17.1, U6.8 (OUT), U6.9 (OUT), U6.10 (OUT), U6.12 (OUT), U6.13 (OUT), U6.14 (OUT)
GND: CN8.2, D4.1 (K), D5.2 (A), R15.2, U6.1 (GND); also elsewhere on the board
unnamed: D4.2 (A), R17.2
unnamed: R16.2, TP17.1, U6.3 (DEN)

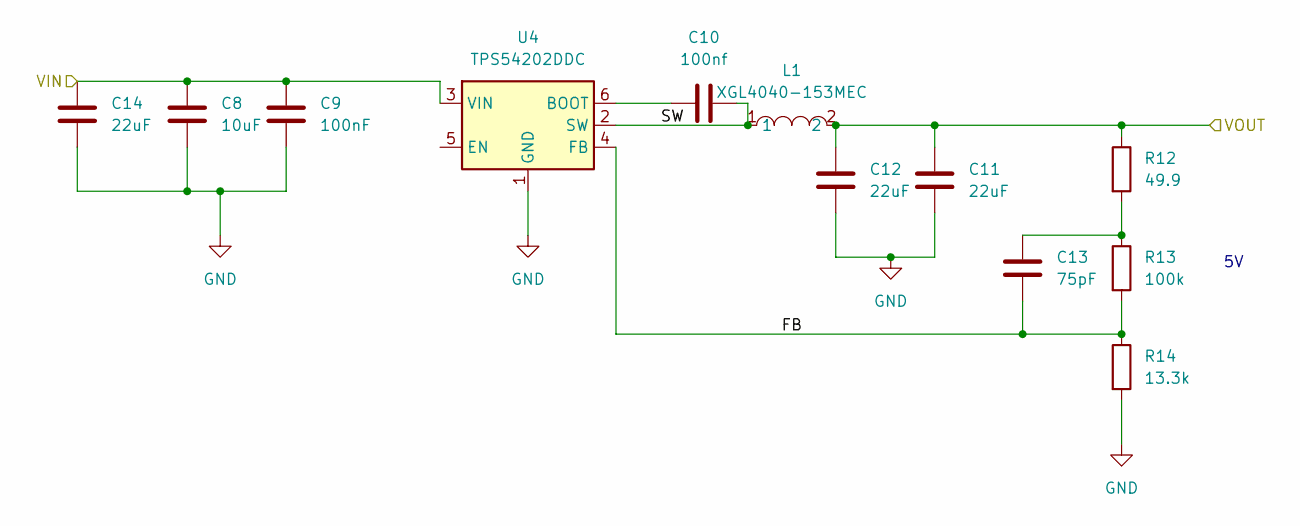
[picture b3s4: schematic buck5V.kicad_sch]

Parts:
C8: 10uF; C_0603_1608Metric
C9: 100nF; C_0603_1608Metric
C10: 100nf; C_0603_1608Metric
C11, C12, C14: 22uF; C_1206_3216Metric
C13: 75pF; C_0603_1608Metric
L1: XGL4040-153MEC; IND-SMD_L4.0-W4.0_XAL4040-103; LCSC Part C3911667
R12: 49.9; R_0603_1608Metric
R13: 100k; R_0603_1608Metric
R14: 13.3k; R_0603_1608Metric
U4: TPS54202DDC; SOT-23-6

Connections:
/buck5V/FB: C13.1, R13.2, R14.1, U4.4 (FB)
/buck5V/SW: C10.2, L1.1, U4.2 (SW)
/buck5V/VIN: C8.1, C9.1, C14.1, U4.3 (VIN); also elsewhere on the board
/buck5V/VOUT: C11.1, C12.1, L1.2, R12.1; also elsewhere on the board
GND: C8.2, C9.2, C11.2, C12.2, C14.2, R14.2, U4.1 (GND); also elsewhere on the board
unnamed: C13.2, R12.2, R13.1
unnamed: C10.1, U4.6 (BOOT)

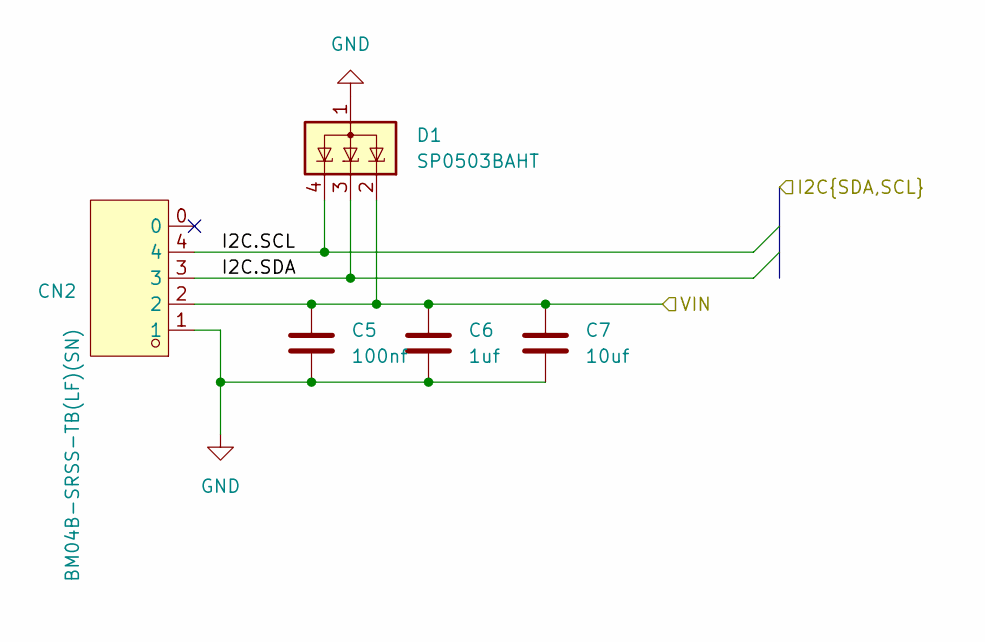
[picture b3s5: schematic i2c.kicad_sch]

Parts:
C5: 100nf; C_0603_1608Metric
C6: 1uf; C_0603_1608Metric
C7: 10uf; C_0603_1608Metric
CN2: BM04B-SRSS-TB(LF)(SN); CONN-SMD_BM04B-SRSS-TB; LCSC Part C160390
D1: SP0503BAHT; SOT-143

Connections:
/i2c1/I2C.SCL: CN2.4, D1.4 (K); also elsewhere on the board
/i2c1/I2C.SDA: CN2.3, D1.3 (K); also elsewhere on the board
/i2c1/VIN: C5.1, C6.1, C7.1, CN2.2, D1.2 (K); also elsewhere on the board
GND: C5.2, C6.2, C7.2, CN2.1, D1.1 (A); also elsewhere on the board

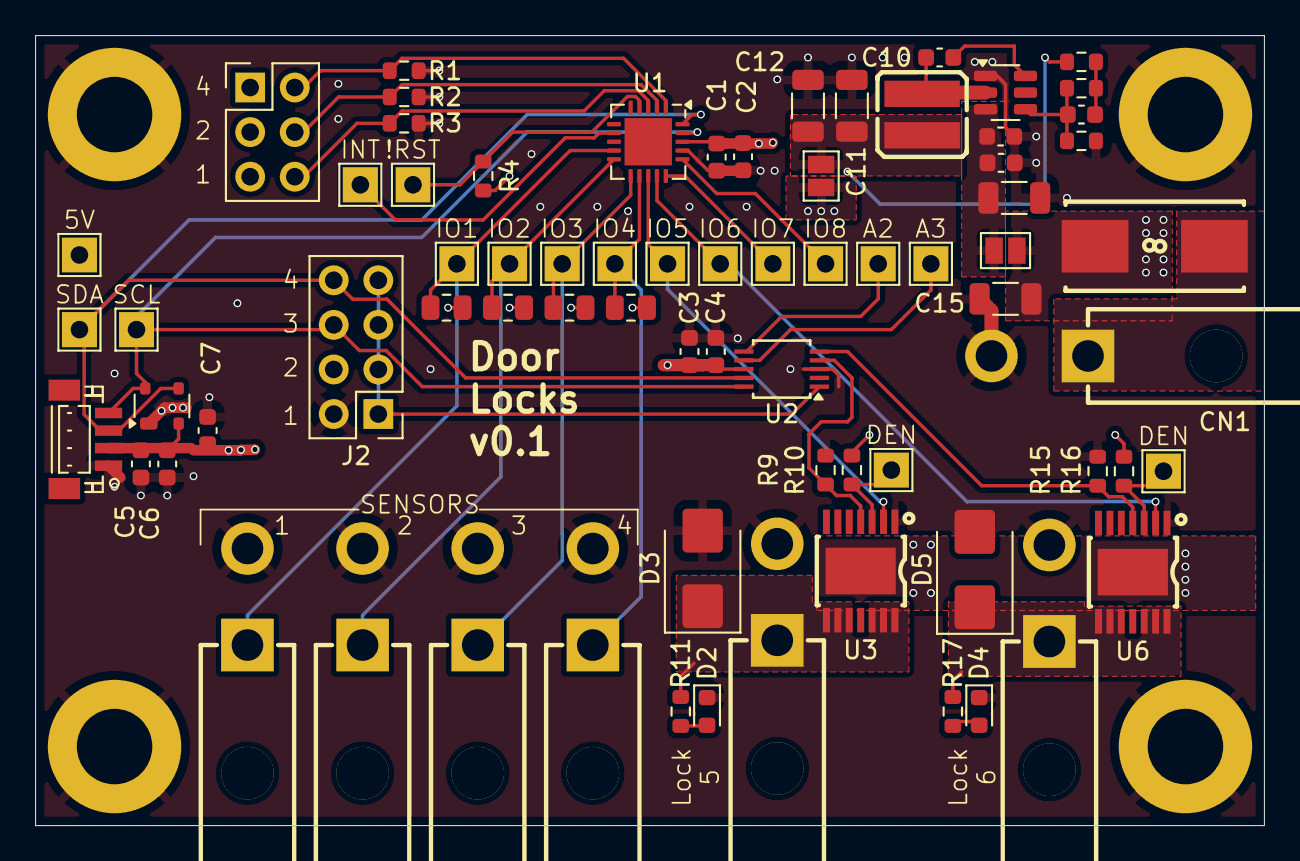
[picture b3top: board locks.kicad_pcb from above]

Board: 4 copper layers, 70.0 x 45.0 mm, 77 parts (0 on the bottom side), 36 nets.

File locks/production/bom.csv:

Designator,Footprint,Quantity,Value,LCSC Part #
"C1, C10, C4, C5, C9",0603,5,100nf,
"C11, C12, C14, C15",1206,4,22uF,
C13,0603,1,75pF,
"C2, C3, C6",0603,3,1uf,
"C7, C8",0603,2,10uf,
"CN1, CN3, CN4, CN5, CN6, CN7, CN8",CONN-TH_2P-P5.50_39-30-1020,7,39-30-1020,C240832
CN2,CONN-SMD_BM04B-SRSS-TB,1,BM04B-SRSS-TB(LF)(SN),C160390
D1,SOT-143,1,SP0503BAHT,
"D2, D4",0603,2,LED,C2286
"D3, D5",D_SMB,2,D_TVS,C151256
FH1,FUSE-SMD_L9.8-W5.0_01550900M,1,01550900M,C108518
J1,PinHeader_2x03_P2.54mm_Vertical,1,Conn_02x03_Odd_Even,C7501274
J2,PinHeader_2x04_P2.54mm_Vertical,1,Conn_02x04_Odd_Even,C5383105
L1,IND-SMD_L4.0-W4.0_XAL4040-103,1,XGL4040-153MEC,C3911667
"R1, R2, R3, R4",0603,4,10k,
"R10, R16",0603,2,4.7k,
"R11, R17",0603,2,3.3k,
R12,0603,1,49.9,
R13,0603,1,100k,
R14,0603,1,13.3k,
"R15, R9",0603,2,1.5k,
"R5, R6, R7, R8",0805,4,3.3k,
U1,QFN-20-1EP_4x4mm_P0.5mm_EP2.7x2.7mm,1,MCP23008-xML,C144211
U2,TSSOP-10_3x3mm_P0.5mm,1,ADS1115IDGS,
"U3, U6",PG-TSDSO-14_L4.9-W3.9-P0.65-LS6.0-BL-EP,2,BTS70021EPPXUMA1,C2680407
U4,SOT-23-6,1,TPS54202DDC,
